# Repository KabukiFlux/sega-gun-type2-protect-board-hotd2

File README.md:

# SEGA Gun type II Input Protection Board for *The House of the Dead 2* 

This repository contains the **KiCAD project files** for the **Gun II Input Protection Board (GIPB)**, a component designed to help protect the gun sensors in *The House of the Dead 2* arcade machines. The design is based on SEGA's **Service Bulletin (09/10/2002)**, which introduced this board to prevent or minimize damage to the **Gun Sense Board** and **LED Boards** caused by connection issues.

## Table of contents

- [Why](#why)
- [Description](#-description)
- [Schematics](#-schematics)
- [Installation Guide](#-installation-guide)
- [Repository contents](#-repository-contents)

## Why?

This was done during some live events on Twitch.tv and tested for some time.

This is a must have for people using the arcade cabinet for guns on a hostile environment

## 📜 Description

Over time, disconnections or improper handling of the gun harnesses can lead to damage in the **Gun Sense Board** or **LED Boards**, potentially rendering the guns non-functional. SEGA introduced this **Gun Input Protection Board** to mitigate this issue. While it **does not repair faulty hardware**, it acts as a safeguard against further damage, extending the lifespan of the arcade cabinet's gun system.  

- **Protects the Gun Sense Board & LED Boards** from connection-related damage  
- **Compatible with original HOTD2 and JPLW arcade hardware**  
- **Straightforward installation** – integrates between the gun harness and the Gun Sense Board  
- **Includes KiCAD project files** for custom PCB manufacturing  

## 📝 Schematics

This is the schematics:

## 🛠️ Installation Guide  

### 1️⃣ Preparation  

1- Send to manufacture the GERBER board to [JLCPCB](https://jlcpcb.com/) or other PCB manufacturer.

2- Get the components required, you can see here the Bill Of Materials [BOM](bom/ibom.html)

3- Solder the components.

Before installing the board, ensure that:  
- The **Gun Sense Board** and **guns are fully functional**  
- The **arcade cabinet is powered off**  

### 2️⃣ Installation Steps  
1. Locate the **Gun Sense Board** inside the arcade machine.  
2. Disconnect the gun harnesses from the **GUN1P** and **GUN2P** ports.  
3. Take the **Gun Input Protection Board (GIPB)** and connect its labeled **GUN1P** and **GUN2P** connectors to the corresponding ports on the **Gun Sense Board**.  
4. Reconnect Player 1’s (Blue Gun) harness into **GUN1P** on the **Protection Board**.  
5. Reconnect Player 2’s (Red Gun) harness into **GUN2P** on the **Protection Board**.  
6. Secure the **Protection Board** using the provided spacers and screws.  
7. Power on the arcade cabinet and enter **Self-Test Mode**.  
8. Navigate to **Gun Settings** and recalibrate the guns.  

## 📝 Repository Contents  

- **`/kicad/`** – KiCAD design files for the **Gun Input Protection Board**  
- **`/bom/`** – Circuit parts and assembly for reference  
- **`/gerbers/`** – Gerber files for PCB fabrication  
- **`/DOC/`** – Original bulletin

## 📢 Disclaimer  

I'm not responsible
===================
And yes, read below, no liability is assumed for misuse.

DISCLAIMER (See Licensing)
==========================
See LICENSE fo more information. 

This project is intended for preservation and repair purposes. **Use at your own risk.** The original SEGA hardware must be in **good working condition** before installation. This repository is **not affiliated with SEGA**.

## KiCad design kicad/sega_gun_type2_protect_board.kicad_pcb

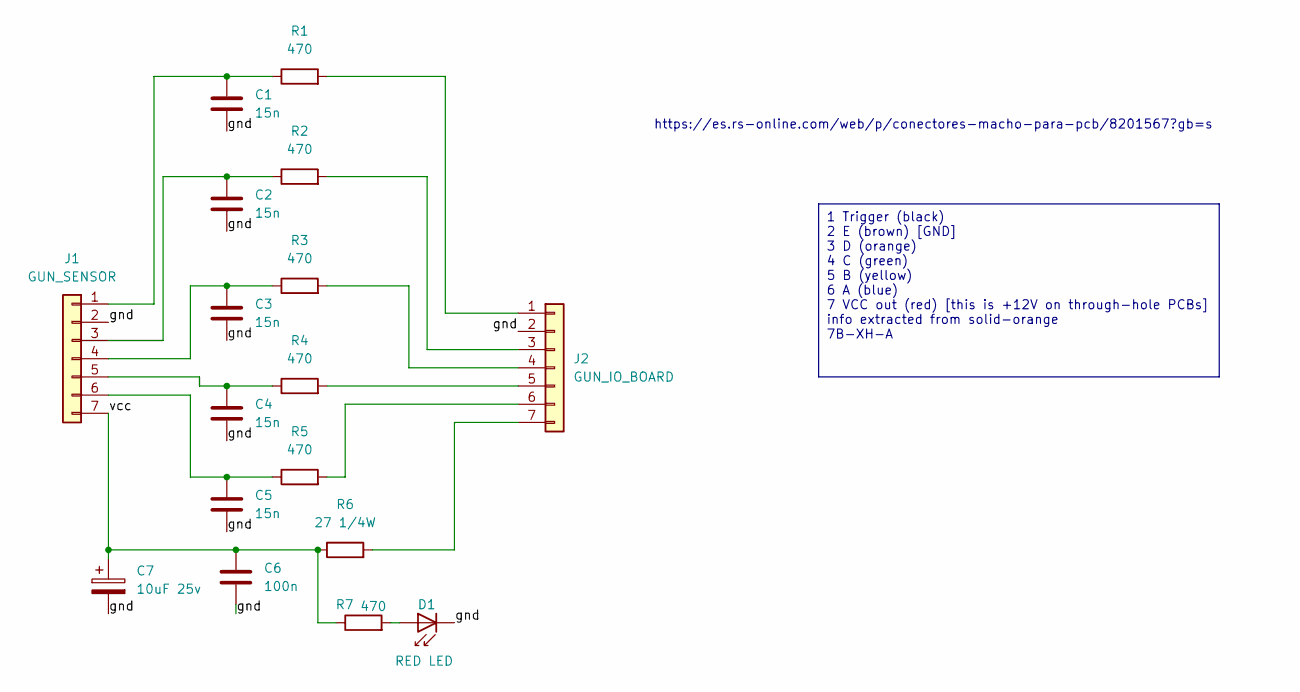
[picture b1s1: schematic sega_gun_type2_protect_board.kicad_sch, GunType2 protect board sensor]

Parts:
C1, C2, C3, C4, C5: 15n; C_Disc_D3.4mm_W2.1mm_P2.50mm
C6: 100n; C_Disc_D3.4mm_W2.1mm_P2.50mm
C7: 10uF 25v; CP_Radial_D6.3mm_P2.50mm
D1: RED LED; LED_D5.0mm_IRGrey
J1: GUN_SENSOR; JST_XH_B7B-XH-A_1x07_P2.50mm_Vertical
J2: GUN_IO_BOARD; PinHeader_1x07_P2.54mm_Vertical
R1, R2, R3, R4, R5, R7: 470; R_Axial_DIN0207_L6.3mm_D2.5mm_P10.16mm_Horizontal
R6: 27 1/4W; R_Axial_DIN0207_L6.3mm_D2.5mm_P10.16mm_Horizontal

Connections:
/gnd: C1.2, C2.1, C3.1, C4.1, C5.1, C6.1, C7.2, D1.1 (K), J1.2, J2.2
/vcc: C6.2, C7.1, J1.7, R6.1, R7.1
unnamed: D1.2 (A), R7.2
unnamed: C1.1, J1.1, R1.1
unnamed: C2.2, J1.3, R2.1
unnamed: C3.2, J1.4, R3.1
unnamed: C4.2, J1.5, R4.1
unnamed: C5.2, J1.6, R5.1
unnamed: J2.1, R1.2
unnamed: J2.3, R2.2
unnamed: J2.4, R3.2
unnamed: J2.5, R4.2
unnamed: J2.6, R5.2
unnamed: J2.7, R6.2

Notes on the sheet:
1 Trigger (black) 2 E (brown) [GND] 3 D (orange) 4 C (green) 5 B (yellow) 6 A (blue) 7 VCC out (red) [this is +12V on through-hole PCBs] info extracted from solid-orange 7B-XH-A
https://es.rs-online.com/web/p/conectores-macho-para-pcb/8201567?gb=s

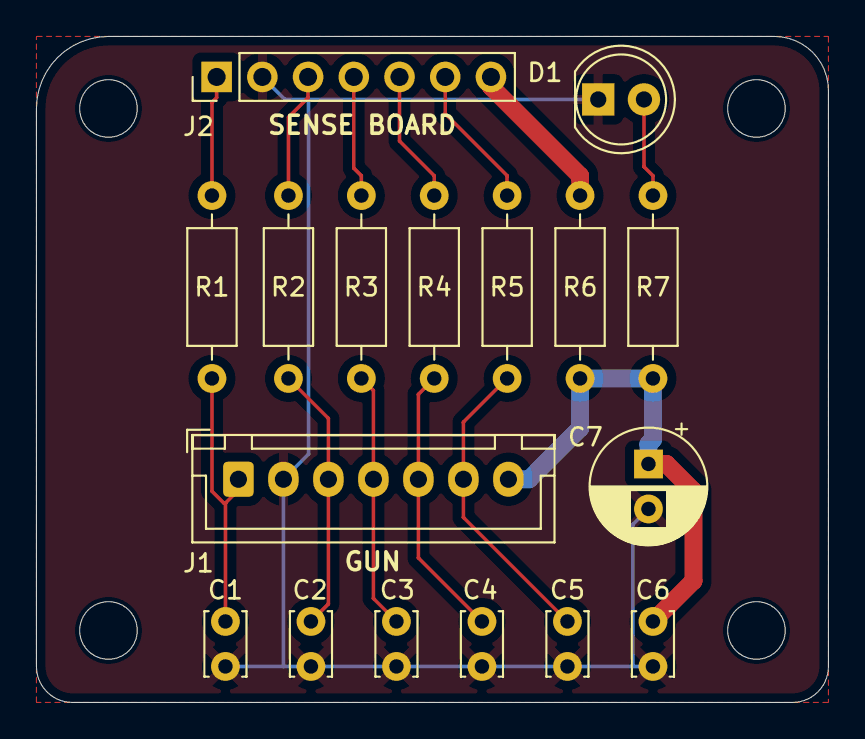
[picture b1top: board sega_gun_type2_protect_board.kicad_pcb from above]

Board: 2 copper layers, 44.0 x 37.0 mm, 21 parts (0 on the bottom side), 14 nets.

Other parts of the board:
REF1, REF2, REF3, REF4: MountingHole_3.2mm_M3

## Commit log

2025-02-17 SEGA / NAMCO Gun Type 2 ohmic protect board upload
